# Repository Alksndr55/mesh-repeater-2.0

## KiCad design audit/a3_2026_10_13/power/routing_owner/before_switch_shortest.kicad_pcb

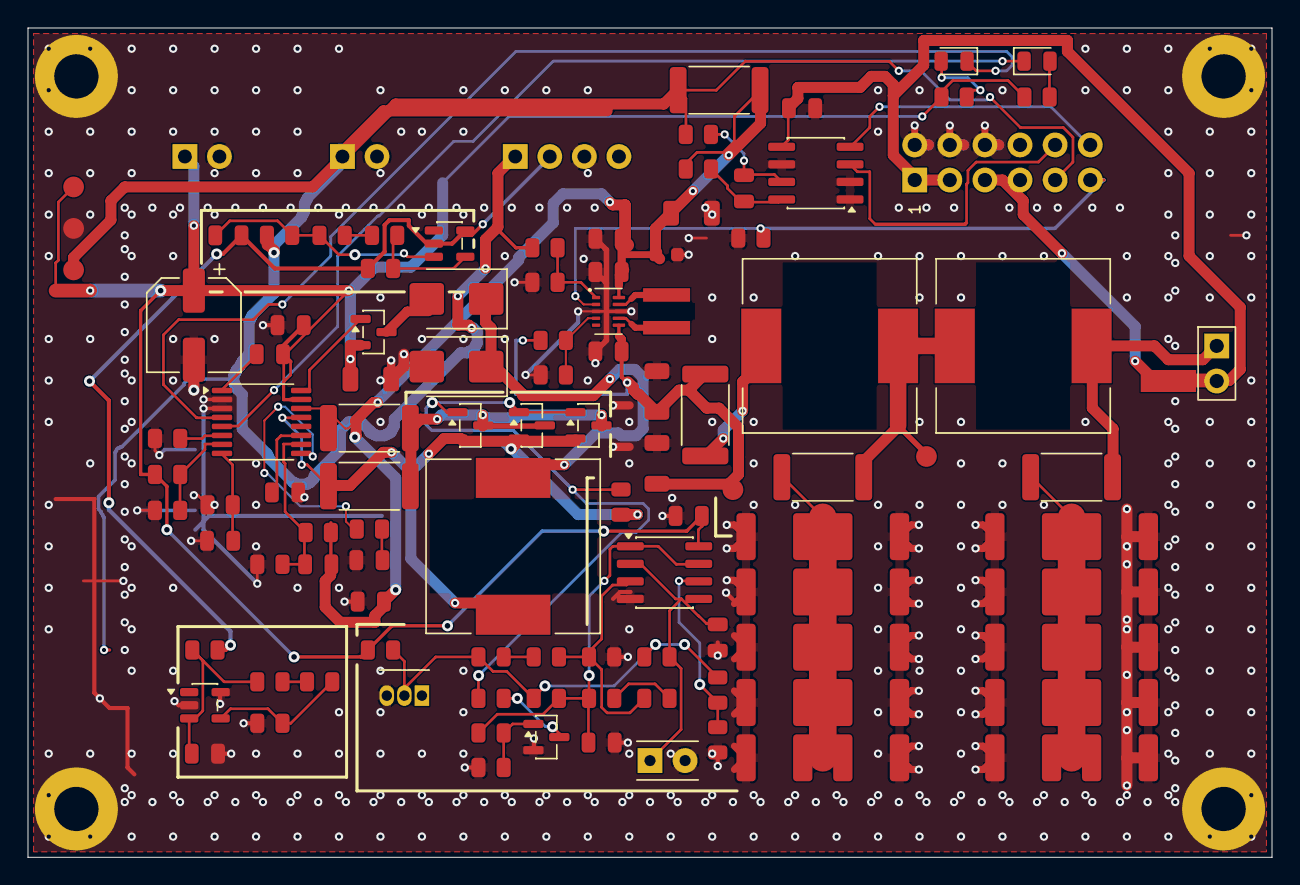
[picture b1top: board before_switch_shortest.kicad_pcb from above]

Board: 2 copper layers, 90.0 x 60.0 mm, 123 parts (0 on the bottom side), 55 nets.

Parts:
C1: 10uF 50V X7R; C_1206_3216Metric__V2_C1
C2: 100nF 50V X7R; C_0805_2012Metric__V2_C2
C3: 100nF 50V X7R; C_0805_2012Metric__V2_C3
C4: 22uF 25V X5R; C_0805_2012Metric__V2_C4
C5: 470pF 50V C0G; C_0805_2012Metric__V2_C5
C6: 220nF 50V X7R; C_0805_2012Metric__V2_C6
C7: 100nF 50V X7R; C_0805_2012Metric__V2_C7
C8: 47uF 35V; CP_Elec_Panasonic_FK_D_6.3x5.8__V2_C8
C12: 10uF 16V X7R; C_0805_2012Metric__V2_C12
C13: 100nF 50V X7R; C_0603_1608Metric__V2_C13
C14: 22uF 25V X5R; C_0805_2012Metric__V2_C14
C15: 100uF; C_1812_4532Metric__V2_C15
C16: 100uF; C_1812_4532Metric__V2_C16
C30: 12pF 50V C0G; C_0805_2012Metric__V2_C30
C34: 100uF; C_1812_4532Metric__V2_C34
C35: 100uF; C_1812_4532Metric__V2_C35
C36: 100uF; C_1812_4532Metric__V2_C36
C37: 100uF; C_1812_4532Metric__V2_C37
C38: 100uF; C_1812_4532Metric__V2_C38
C39: 100uF; C_1812_4532Metric__V2_C39
C40: 100uF; C_1812_4532Metric__V2_C40
C41: 100uF; C_1812_4532Metric__V2_C41
C42: 100uF; C_1812_4532Metric__V2_C42
C43: 100uF; C_1812_4532Metric__V2_C43
C44: 100uF; C_1812_4532Metric__V2_C44
C45: 100uF; C_1812_4532Metric__V2_C45
C46: 100uF; C_1812_4532Metric__V2_C46
C47: 100uF; C_1812_4532Metric__V2_C47
C48: 100uF; C_1812_4532Metric__V2_C48
C49: 100uF; C_1812_4532Metric__V2_C49
C50: 100uF; C_1812_4532Metric__V2_C50
C51: 100uF; C_1812_4532Metric__V2_C51
C52: 10uF 16V X7R; C_0805_2012Metric__V2_C52
C53: DNP; C_1206_3216Metric__V2_C53
C54: DNP; C_1206_3216Metric__V2_C54
C55: DNP; C_1206_3216Metric__V2_C55
C58: 47nF 16V X7R; C_0805_2012Metric__V2_C58
C59: 47nF 16V X7R; C_0805_2012Metric__V2_C59
C60: 100nF 100V X7R; C_0805_2012Metric__V2_C60
C61: 1nF 100V C0G; C_0805_2012Metric__V2_C61
C62: 100nF 100V X7R; C_0805_2012Metric__V2_C62
C63: 100nF 50V X7R; C_0805_2012Metric__V2_C63
C64: 100nF 50V X7R; C_0805_2012Metric__V2_C64
D1: SS24; D_SMB__V2_D1
D2: SS24; D_SMB__V2_D2
D3: RED; LED_0805_2012Metric__V2_D3
D4: GREEN; LED_0805_2012Metric__V2_D4
H1: M3 GND contact; GND_M3_D3.2_OD6__V2_H1
H2: M3 GND contact; GND_M3_D3.2_OD6__V2_H2
H3: M3 GND contact; GND_M3_D3.2_OD6__V2_H3
H4: M3 GND contact; GND_M3_D3.2_OD6__V2_H4
J7: SOLAR 12V; JST_XH_S2B-XH-A_1x02_P2.50mm_Horizontal__V2_J7
J8: Na-ion; JST_XH_S2B-XH-A_1x02_P2.50mm_Horizontal__V2_J8
J11: LC OUT - 3V3; Connfly_DS1022_1x02RUF11_B_Horizontal
J12: LTO; KLS_XH_L_KLS1_2_50_04_R_Horizontal__V2_J12
J101: INTERBOARD 2x6 VERTICAL; Ali_PinHeader_2x06_P2.54_L35_A3C6__V2_J101
L1: 100uH; L_Sumida_CDRH127_LDNP_101MC__V2_L1
L2: 0.47uH; L_Coilcraft_XGL4020_471MEC__V2_L2
L3: 2.4uH; L_Sumida_CDRH127_LD__V2_L3
L4: 2.4uH; L_Sumida_CDRH127_LD__V2_L4
NT2: 3V3 STAR; NetTie_2_SMD_Power_Star_A3
Q1: AO3401A; SOT-23__V2_Q1
Q4: AO3401A; SOT-23__V2_Q4
Q5: BSS138; SOT-23__V2_Q5
Q6: AO3401A; SOT-23__V2_Q6
Q7: AO3401A; SOT-23__V2_Q7
R1: 0.28R 1%; R_2512_6332Metric__A3_R1
R3: 61.9k 0.1% <=25ppm/C; R_0805_2012Metric__V2_R3
R4: 100k 0.1% <=25ppm/C; R_0805_2012Metric__V2_R4
R5: 1M 0.1%; R_0805_2012Metric__V2_R5
R6: 120R; R_0805_2012Metric__V2_R6
R7: 105k 0.1%; R_0805_2012Metric__V2_R7
R8: 10k 0.1%; R_0805_2012Metric__V2_R8
R9: 10k; R_0805_2012Metric__V2_R9
R10: 10k; R_0805_2012Metric__V2_R10
R11: 10k; R_0805_2012Metric__V2_R11
R13: 56k 0.1%; R_0805_2012Metric__V2_R13
R14: 10k 0.1%; R_0805_2012Metric__V2_R14
R15: 40.2k 0.1%; R_0805_2012Metric__V2_R15
R16: 49.9k 0.1%; R_0805_2012Metric__V2_R16
R17: 100k; R_0805_2012Metric__V2_R17
R40: 22mR 1%; R_2512_6332Metric__A3_R40
R41: 22mR 1%; R_2512_6332Metric__A3_R41
R47: 2R 1%; R_0805_2012Metric__V2_R47
R48: 120k 0.1%; R_0805_2012Metric__V2_R48
R49: 2.49k 0.1%; R_0805_2012Metric__V2_R49
R50: 100k 0.1%; R_0805_2012Metric__V2_R50
R51: 2R 1%; R_0805_2012Metric__V2_R51
R52: 120k 0.1%; R_0805_2012Metric__V2_R52
R53: 2.49k 0.1%; R_0805_2012Metric__V2_R53
R54: 100k 0.1%; R_0805_2012Metric__V2_R54
R55: 47mR 1%; R_2512_6332Metric__A3_R55
R56: 1.8R 1% 1W; R_2512_6332Metric__A3_R56
R57: 47k 1% 0.125W; R_0805_2012Metric__V2_R57
R58: 100k 1%; R_0805_2012Metric__V2_R58
R59: 100k 1%; R_0805_2012Metric__V2_R59
R60: 100k 1%; R_0805_2012Metric__V2_R60
R61: 100k 1%; R_0805_2012Metric__V2_R61
R62: 1M 1%; R_0805_2012Metric__V2_R62
R63: 100k 1%; R_0805_2012Metric__V2_R63
R64: 1.2M 1%; R_0805_2012Metric__V2_R64
R65: 10k 1%; R_0805_2012Metric__V2_R65
R66: 1k 1%; R_0805_2012Metric__V2_R66
R67: 1M 1%; R_0805_2012Metric__V2_R67
R68: 1k 1%; R_0805_2012Metric__V2_R68
R69: 30k 1%; R_0805_2012Metric__V2_R69
R70: 150k 1%; R_0805_2012Metric__V2_R70
R71: 0.1R 1% 1W; R_2512_6332Metric__A3_R71
R72: 10R 1%; R_0805_2012Metric__V2_R72
R73: 10R 1%; R_0805_2012Metric__V2_R73
TH1: 10k NTC 1% B3988; NTC_TDK_B57861S_Onboard_or_Remote_P2.54mm__V2_TH1
TP1: BAT; TestPoint_Pad_D1.5mm__V2_TP1
TP3: SYS_PRE; TestPoint_Pad_D1.5mm__V2_TP3
TP6: GND; TestPoint_Pad_D1.5mm__V2_TP6
TP8: FILTER_MID; TestPoint_Pad_D1.5mm__V2_TP8
TP9: SOLAR; TestPoint_Pad_D1.5mm__V2_TP9
U1: CN3722; TSSOP-16_4.4x5mm_P0.65mm__V2_U1
U2: TPS63802DLAR; TPS63802_DLA0010A__V2_U2
U8: LMV431A; SOT-23-5__V2_U8
U9: LMV431A; SOT-23-5__V2_U9
U10: LM393XK; SOIC-8_3.9x4.9mm_P1.27mm__V2_U10
U11: LM285Z-2.5G; TO-92_Inline__V2_U11
U12: INA219AIDR; SOIC-8_3.9x4.9mm_P1.27mm__V2_U12

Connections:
/2. Converter/EN_UV: R15.2, R16.1, U2.1 (EN)
/2. Converter/FB_SYS: R13.2, R14.1, U2.4 (FB)
/2. Converter/FILTER_MID: L3.2, L4.1, R40.1, TP8.1
/2. Converter/LX1: L2.1, U2.9 (L1)
/2. Converter/LX2: L2.2, U2.7 (L2)
/2. Converter/SYS_LC_IN: L3.1, R55.2
/2. Converter/SYS_PRE: C14.1, C54.1, C55.1, R13.1, R55.1, TP3.1, U2.6 (VOUT)
/4. Thermal/CHG_G_ENABLE: Q5.1, R66.2, R67.1
/4. Thermal/CHG_HYST_MID: R62.2, R70.1
/4. Thermal/CHG_PULLDOWN: Q5.3, R68.2
/4. Thermal/CHG_TSENSE: C61.1, R59.2, TH1.1, U10.2, U10.5
/4. Thermal/CHG_VREF: R57.2, R59.1, R60.1, R63.1, R64.1, U11.2
/4. Thermal/CHG_VSHORT: R64.2, R65.1, U10.6
/4. Thermal/CHG_VTH: R61.1, R69.2, R70.2, U10.3
/4. Thermal/CHG_VTH_UP: R60.2, R69.1
/4. Thermal/CHG_WARM: C62.1, R62.1, R63.2, R66.1, U10.1, U10.7
/GATE: Q1.1 (G), U1.16 (DRV)
BAT: J8.1, J12.1, J101.9, R15.1, R47.1, R71.2, R73.1, TP1.1
BAT_SYS: C4.1, C12.1, C13.1, C30.1, C52.1, C53.1, R1.2, R3.1, R71.1, R72.1, U1.14 (BAT), U2.10 (VIN)
CHG_CS_M: Q4.3, Q6.3, Q7.3, R1.1, R56.2
CHG_G_SHUNT: Q4.1, Q6.1, Q7.1, R58.2, R68.1
CHRG: D3.1 (K), U1.4 (CHRG)
CS_P: L1.2, Q4.2, Q6.2, Q7.2, R56.1, R58.1, U1.13 (CSP)
DONE: D4.1 (K), U1.5 (DONE)
FILTER_OUT: J11.1, L4.2, R41.1
GND: C1.2, C2.2, C4.2, C5.2, C6.2, C7.2, C8.2, C12.2, C13.2, C14.2, C15.2, C16.2, C34.2, C35.2, C36.2, C37.2, C38.2, C39.2, C40.2, C41.2, C42.2, C43.2, C44.2, C45.2, C46.2, C47.2, C48.2, C49.2, C50.2, C51.2, C52.2, C53.2, C54.2, C55.2, C59.2, C60.2, C61.2, C62.2, C63.2, D2.2 (A), H1.1, H2.1, H3.1, H4.1, J7.2, J8.2, J12.3, J101.2, J101.4, J101.6, Q5.2, R4.2, R5.2, R8.2, R9.2, R14.2, R16.2, R17.2, R54.2, R61.2, R65.2, R67.2, TH1.2, TP6.1, U1.2 (PGND), U1.3 (GND), U2.3 (AGND), U2.8 (PGND), U9.2 (A), U9.5 (A), U10.4, U11.3, U12.1, U12.2, U12.6
LTO_MID: C58.2, J12.2, R50.2, R51.1, U8.2 (A), U8.5 (A)
MODE: J101.11, R17.1, U2.2 (MODE)
unnamed: C6.1, R6.2
unnamed: C15.1, C34.1, C35.1, C36.1, C37.1, C38.1, C39.1, C40.1, C41.1, C42.1, R40.2
unnamed: C16.1, C43.1, C44.1, C45.1, C46.1, C47.1, C48.1, C49.1, C50.1, C51.1, R41.2
unnamed: D1.2 (A), Q1.3 (D)
unnamed: D1.1 (K), D2.1 (K), L1.1
unnamed: D3.2 (A), R10.2
unnamed: D4.2 (A), R11.2
unnamed: R48.2, R49.1
unnamed: R52.2, R53.1
unnamed: C5.1, R5.1, U1.8 (COM1)
unnamed: R6.1, U1.9 (COM2)
unnamed: C7.1, U1.11 (COM3)
unnamed: C30.2, R3.2, R4.1, U1.10 (FB)
unnamed: R7.2, R8.1, U1.7 (MPPT)
unnamed: R9.1, U1.6 (TEMP)
unnamed: C3.2, U1.1 (VG)
unnamed: C58.1, R47.2, R48.1, U8.3 (K)
unnamed: R49.2, R50.1, U8.4 (REF)
unnamed: C59.1, R51.2, R52.1, U9.3 (K)
unnamed: R53.2, R54.1, U9.4 (REF)
unnamed: C64.1, R72.2, U12.8
unnamed: C64.2, R73.2, U12.7
RADIO_3V3: J101.5, J101.7, NT2.2
SCL: J101.12, U12.4
SDA: J101.10, U12.3
SOLAR: C1.1, C2.1, C3.1, C8.1, C60.1, J7.1, Q1.2 (S), R7.1, R10.1, R11.1, R57.1, TP9.1, U1.15 (VCC), U10.8
SYS_3V3: C63.1, J11.2, J101.1, J101.3, NT2.1, U12.5
